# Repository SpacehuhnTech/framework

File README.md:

# ESP32-S3 Framework Expansion Card 

Here are the KiCAD files of my ESP32-S3 Expansion Card for the Framework Laptop.
Learn more about my project on YouTube: https://youtu.be/IML9c_MsyQU

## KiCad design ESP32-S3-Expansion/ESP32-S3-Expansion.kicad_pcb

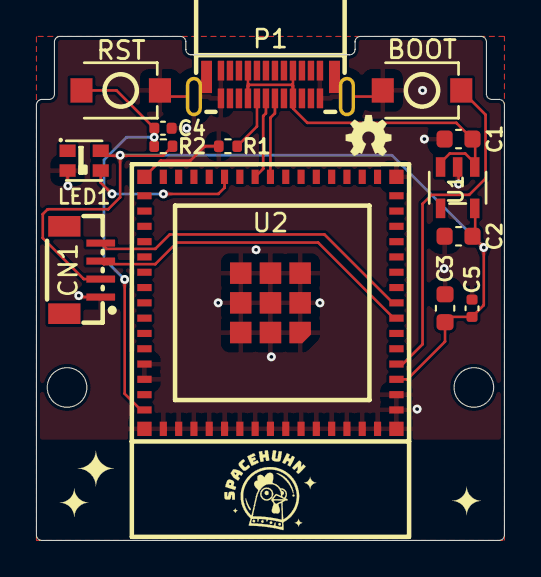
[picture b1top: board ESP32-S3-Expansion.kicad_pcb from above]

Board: 2 copper layers, 26.0 x 28.0 mm, 21 parts (1 on the bottom side), 11 nets.

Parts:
C1, C2: 1uF; C_0603_1608Metric
C3: 22uF; C_0603_1608Metric
C4, C5: 100nF; C_0402_1005Metric
CN1: 1.0T-4PLTPZ; FPC-SMD_4P-P1.00_1.0T-4PLTPZ
G1: LOGO; spacehuhn_logo_text_big-mask
G2: LOGO; star_small
G3, G4: LOGO; star_tiny
G5: LOGO; oshw_logo_small
H1, H2: MountingHole; MountingHole_2.2mm_M2
LED1: WS2812B-2020; LED-SMD_4P-L2.0-W2.0-TL_WS2812B-2020
P1: USB_C_Plug_USB2.0; USB-C-SMD_TYPEC-951-ARP24
R1: 5.1k; R_0402_1005Metric
R2: 10K; R_0402_1005Metric
SW1, SW2: TS-1088-AR02016; SW-SMD_L3.9-W3.0-P4.45
U1: AP2112K-3.3TRG1; SOT-25-5_AP2112K
U2: ESP32-S3-MINI-1-N4R2

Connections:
+3V3: C2.1, C3.1, C5.1, CN1.2, LED1.4 (VDD), R2.2, U1.5 (VOUT), U2.3 (3V3)
+5V: C1.1, P1.A4 (VBUS), P1.A9 (VBUS), P1.B4 (VBUS), P1.B9 (VBUS), U1.1 (VIN), U1.3 (EN)
/BOOT: SW2.1, U2.4 (IO0)
/D+: P1.A6 (D+), U2.24 (IO20)
/D-: P1.A7 (D-), U2.23 (IO19)
/NPXL: LED1.3 (DI), U2.26 (IO26)
/RESET: C4.1, R2.1, SW1.2, U2.45 (EN)
/SCL: CN1.4, U2.8 (IO4)
/SDA: CN1.3, U2.7 (IO3)
GND: C1.2, C2.2, C3.2, C4.2, C5.2, CN1.1, LED1.2 (GND), P1.25 (SHIELD), P1.26 (SHIELD), P1.A1 (GND), P1.A12 (GND), P1.B1 (GND), P1.B12 (GND), R1.2, SW1.1, SW2.2, U1.2 (GND), U2.1 (GND), U2.2 (GND), U2.42 (GND), U2.43 (GND), U2.46 (GND), U2.47 (GND), U2.48 (GND), U2.49 (GND), U2.50 (GND), U2.51 (GND), U2.52 (GND), U2.53 (GND), U2.54 (GND), U2.55 (GND), U2.56 (GND), U2.57 (GND), U2.58 (GND), U2.59 (GND), U2.60 (GND), U2.61 (GND), U2.62 (GND), U2.63 (GND), U2.64 (GND), U2.65 (GND)
unnamed: P1.A5 (CC), R1.1

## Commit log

2023-06-26 Addef files

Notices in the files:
ESP32-S3-Expansion/ESP32-S3-Expansion.kicad_pcb:
This work is licensed under a Creative Commons Attribution 4.0 International License
